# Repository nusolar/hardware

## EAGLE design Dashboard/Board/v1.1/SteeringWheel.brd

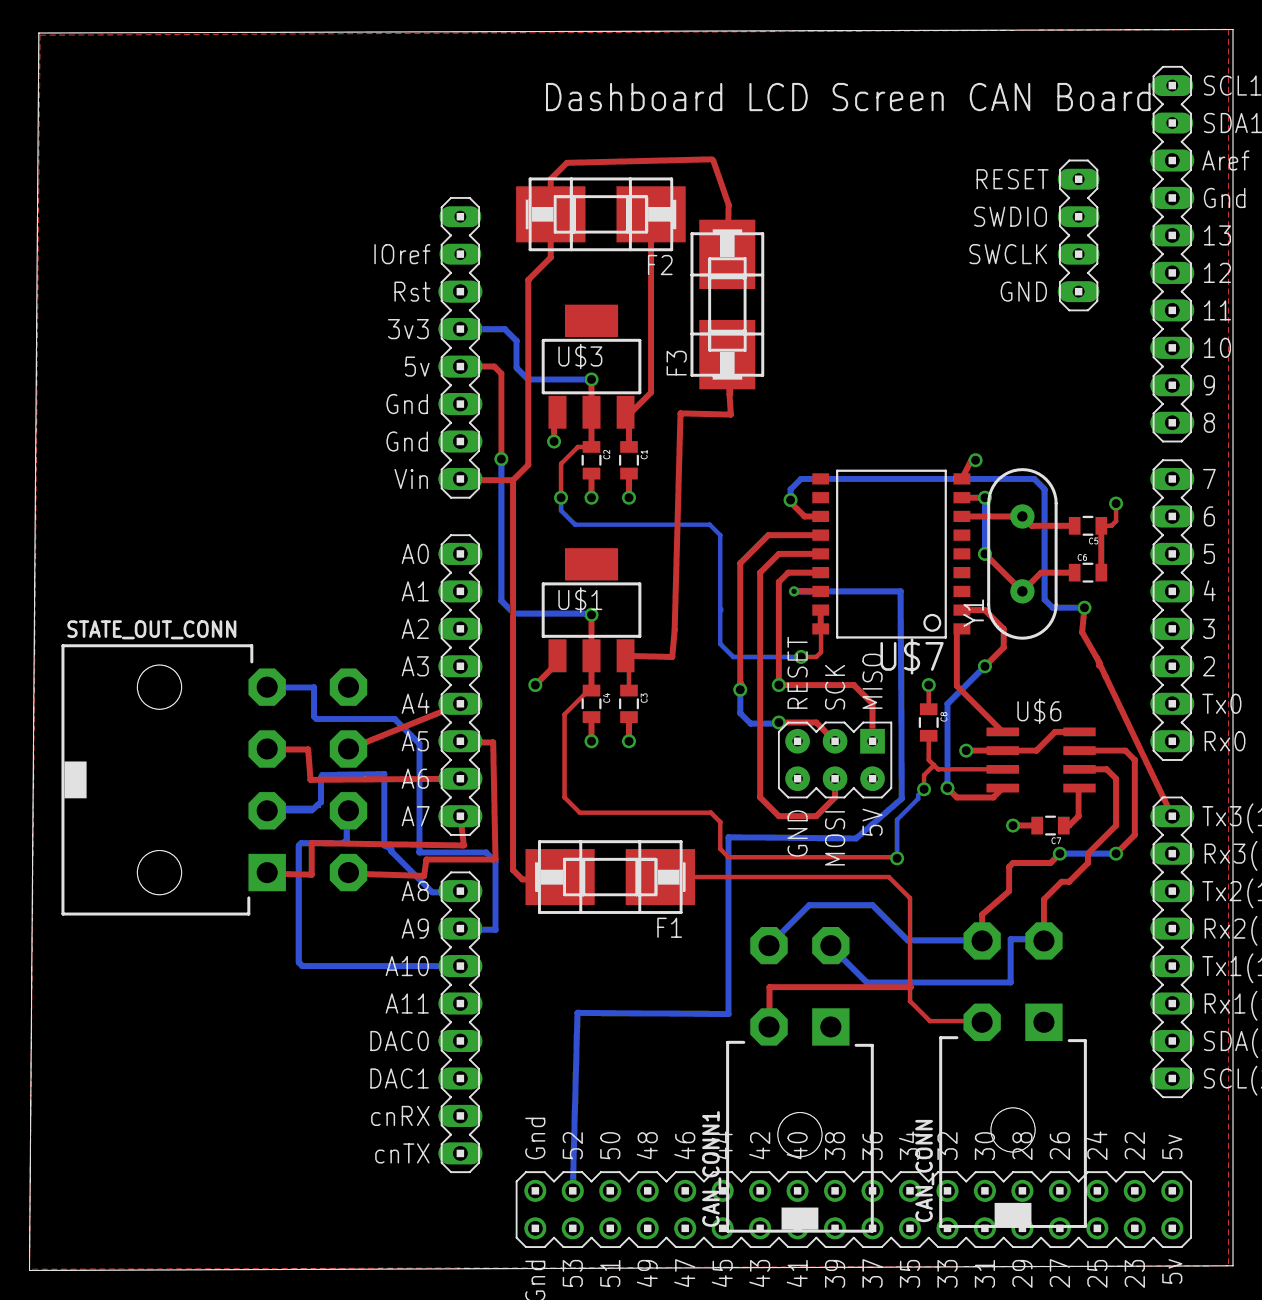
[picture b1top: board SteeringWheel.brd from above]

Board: 2 copper layers, 81.6 x 84.1 mm, 20 parts (0 on the bottom side), 25 nets.

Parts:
C1, C2, C3, C4, C7, C8: .1µF; 0805
C5, C6: 0805
CAN_CONN, CAN_CONN1: 39-30-04?; 39-30-?04?
F1, F2, F3: SMD-MICRO-FUSE-BLOCK; OMNIBLOK
STATE_OUT_CONN: 39-30-08?; 39-30-?08?
U$1: NCP1117ST50T3G; SOT223
U$2: DUE(NORMAL)
U$3: NCP1117ST33T3G; SOT223
U$6: MCP2562; SOIC8
U$7: MCP2515; SO-18W
Y1: HC49US

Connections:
3.3V: C2.1, C7.1, U$2.3V3, U$3.2, U$6.5, U$7.17, U$7.18
5V: C4.1, C8.2, U$1.2, U$2.5V, U$6.3
12V: F1.P$2, F2.P$2, F3.P$2, U$2.VIN
BRK: STATE_OUT_CONN.3, U$2.A6
CAN+: CAN_CONN.2, CAN_CONN1.2, F1.P$1
CAN_CS: U$2.52, U$7.16
CAN_H: CAN_CONN.4, CAN_CONN1.4, U$6.7
CAN_INT: U$2.TX3, U$7.12
CAN_L: CAN_CONN.3, CAN_CONN1.3, U$6.6
CAN_RX: U$6.4, U$7.2
CAN_TX: U$6.1, U$7.1
GND: C1.2, C2.2, C3.2, C4.2, C5.1, C6.2, C7.2, C8.1, CAN_CONN.1, CAN_CONN1.1, U$1.1, U$2.GND_1, U$2.GND_2, U$3.1, U$6.2, U$6.8, U$7.9
HAZ: STATE_OUT_CONN.5, U$2.A5
HD: STATE_OUT_CONN.7, U$2.A4
HRN: STATE_OUT_CONN.2, U$2.A8
LT: STATE_OUT_CONN.4, U$2.A9
MISO: U$2.MISO_ICSP, U$7.15
MOSI: U$2.MOSI_ICSP, U$7.14
unnamed: C3.1, F3.P$1, U$1.3
unnamed: C1.1, F2.P$1, U$3.3
unnamed: C5.2, U$7.7, Y1.2
unnamed: C6.1, U$7.8, Y1.1
RT: STATE_OUT_CONN.6, U$2.A10
SCK: U$2.SCK_ICSP, U$7.13
STRB: STATE_OUT_CONN.1, U$2.A7

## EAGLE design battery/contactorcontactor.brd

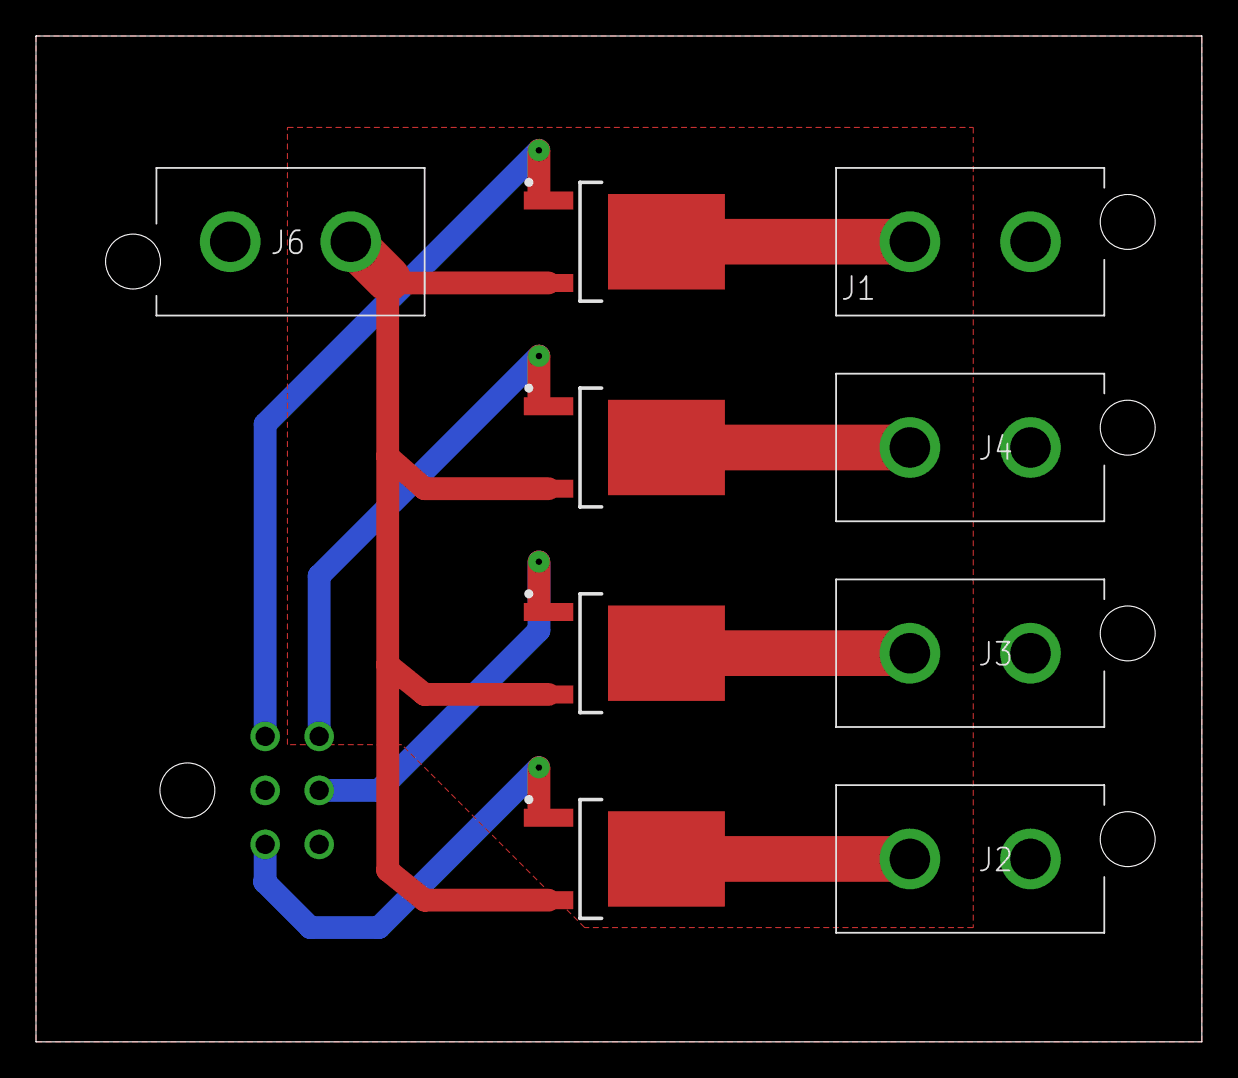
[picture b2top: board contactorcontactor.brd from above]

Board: 2 copper layers, 64.8 x 55.9 mm, 10 parts (1 on the bottom side), 10 nets.

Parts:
J1, J2, J3, J4, J6: 15-31-1026; 15311026
J5: 0430450600; 0430450601
Q1, Q2, Q3, Q4: SPD04P10PL_G; TO229P994X241-3N

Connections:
ASDF: J5.1, Q1.1
GND: J1.2, J2.2, J3.2, J4.2, J5.6, J6.2
unnamed: J2.1, Q2.2
unnamed: J3.1, Q4.2
unnamed: J4.1, Q3.2
unnamed: J1.1, Q1.2
unnamed: J6.1, Q1.3, Q2.3, Q3.3, Q4.3
unnamed: J5.5, Q4.1
unnamed: J5.3, Q2.1
unnamed: J5.4, Q3.1

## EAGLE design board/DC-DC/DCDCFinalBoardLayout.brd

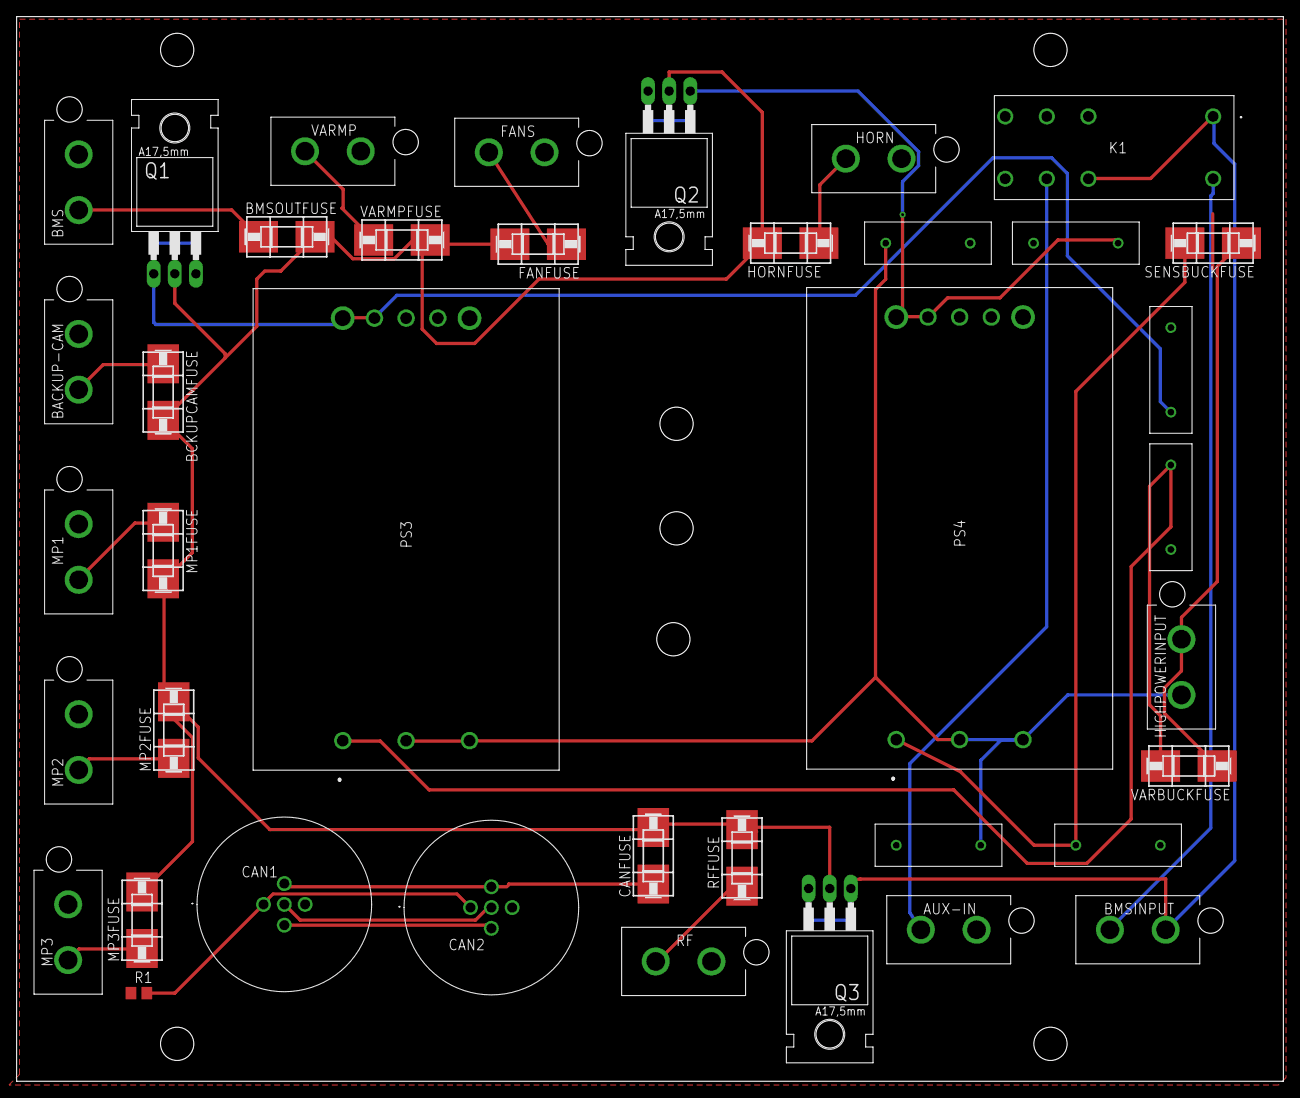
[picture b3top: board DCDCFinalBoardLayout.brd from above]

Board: 2 copper layers, 152.3 x 128.0 mm, 39 parts (0 on the bottom side), 24 nets.

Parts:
AUX-IN: 15-31-1026; 15311026
BACKUP-CAM: 15-31-1026; 15311026
BCKUPCAMFUSE: .25; OMNIBLOK
BMS: 15-31-1026; 15311026
BMSINPUT: 15-31-1026; 15311026
BMSOUTFUSE: 1.2A; OMNIBLOK
CAN1, CAN2: 1200845179
CANFUSE: 1.3 A; OMNIBLOK
FANFUSE: 6 A; OMNIBLOK
FANS: 15-31-1026; 15311026
HIGHPOWERINPUT: 15-31-1026; 15311026
HORN: 15-31-1026; 15311026
HORNFUSE: 1.5 A; OMNIBLOK
K1: ALZ12B12W
MP1, MP2, MP3: 15-31-1026; 15311026
MP1FUSE, MP2FUSE, MP3FUSE: 1A; OMNIBLOK
PS3, PS4: IRQ-12_8.3-T110N-C; IRQ1283T110NC
Q1, Q2, Q3: BUZ10; TO220
R1: 0; R0805
RF: 15-31-1026; 15311026
RFFUSE: 0.4 A; OMNIBLOK
SENSBUCKFUSE: 2A; OMNIBLOK
U$1, U$3, U$4, U$5, U$7, U$8: 4700PF; Y2_CAP
VARBUCKFUSE: 2A; OMNIBLOK
VARMP: 15-31-1026; 15311026
VARMPFUSE: 0.7 A; OMNIBLOK

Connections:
12V: BCKUPCAMFUSE.P$2, BMSOUTFUSE.P$2, CANFUSE.P$2, FANFUSE.P$2, HORNFUSE.P$2, MP1FUSE.P$2, MP2FUSE.P$2, MP3FUSE.P$2, Q1.2, Q2.2, Q3.2, RFFUSE.P$2, VARMPFUSE.P$2
CAN+: BACKUP-CAM.1, BCKUPCAMFUSE.P$1
GND: AUX-IN.2, BACKUP-CAM.2, BMS.2, CAN1.3, CAN2.3, FANS.2, HORN.2, MP1.2, MP2.2, MP3.2, PS3.4, PS3.5, PS4.4, PS4.5, R1.1, RF.2, U$1.P$2, U$3.P$2, U$4.P$1, U$5.P$1, U$7.P$1, U$8.P$1, VARMP.2
IN(-): HIGHPOWERINPUT.1, PS3.2, PS3.3, PS4.2, PS4.3, U$1.P$1, U$3.P$1
IN+: HIGHPOWERINPUT.2, SENSBUCKFUSE.P$1, VARBUCKFUSE.P$1
unnamed: HORN.1, HORNFUSE.P$1
unnamed: AUX-IN.1, K1.6
unnamed: BMSINPUT.1, K1.8
unnamed: BMSINPUT.2, K1.1, K1.7, Q3.1, Q3.3
unnamed: PS3.1, U$7.P$2, VARBUCKFUSE.P$2
unnamed: VARMP.1, VARMPFUSE.P$1
unnamed: RF.1, RFFUSE.P$1
unnamed: FANFUSE.P$1, FANS.1
unnamed: PS4.1, SENSBUCKFUSE.P$2, U$4.P$2
unnamed: BMS.1, BMSOUTFUSE.P$1
unnamed: MP2.1, MP2FUSE.P$1
unnamed: MP3.1, MP3FUSE.P$1
unnamed: PS3.7, PS3.8, Q1.1, Q1.3, U$8.P$2
unnamed: MP1.1, MP1FUSE.P$1
unnamed: PS4.7, PS4.8, Q2.1, Q2.3, U$5.P$2
unnamed: CAN1.1, CAN2.1, R1.2
unnamed: CAN1.4, CAN2.4
unnamed: CAN1.5, CAN2.5
unnamed: CAN1.2, CAN2.2, CANFUSE.P$1

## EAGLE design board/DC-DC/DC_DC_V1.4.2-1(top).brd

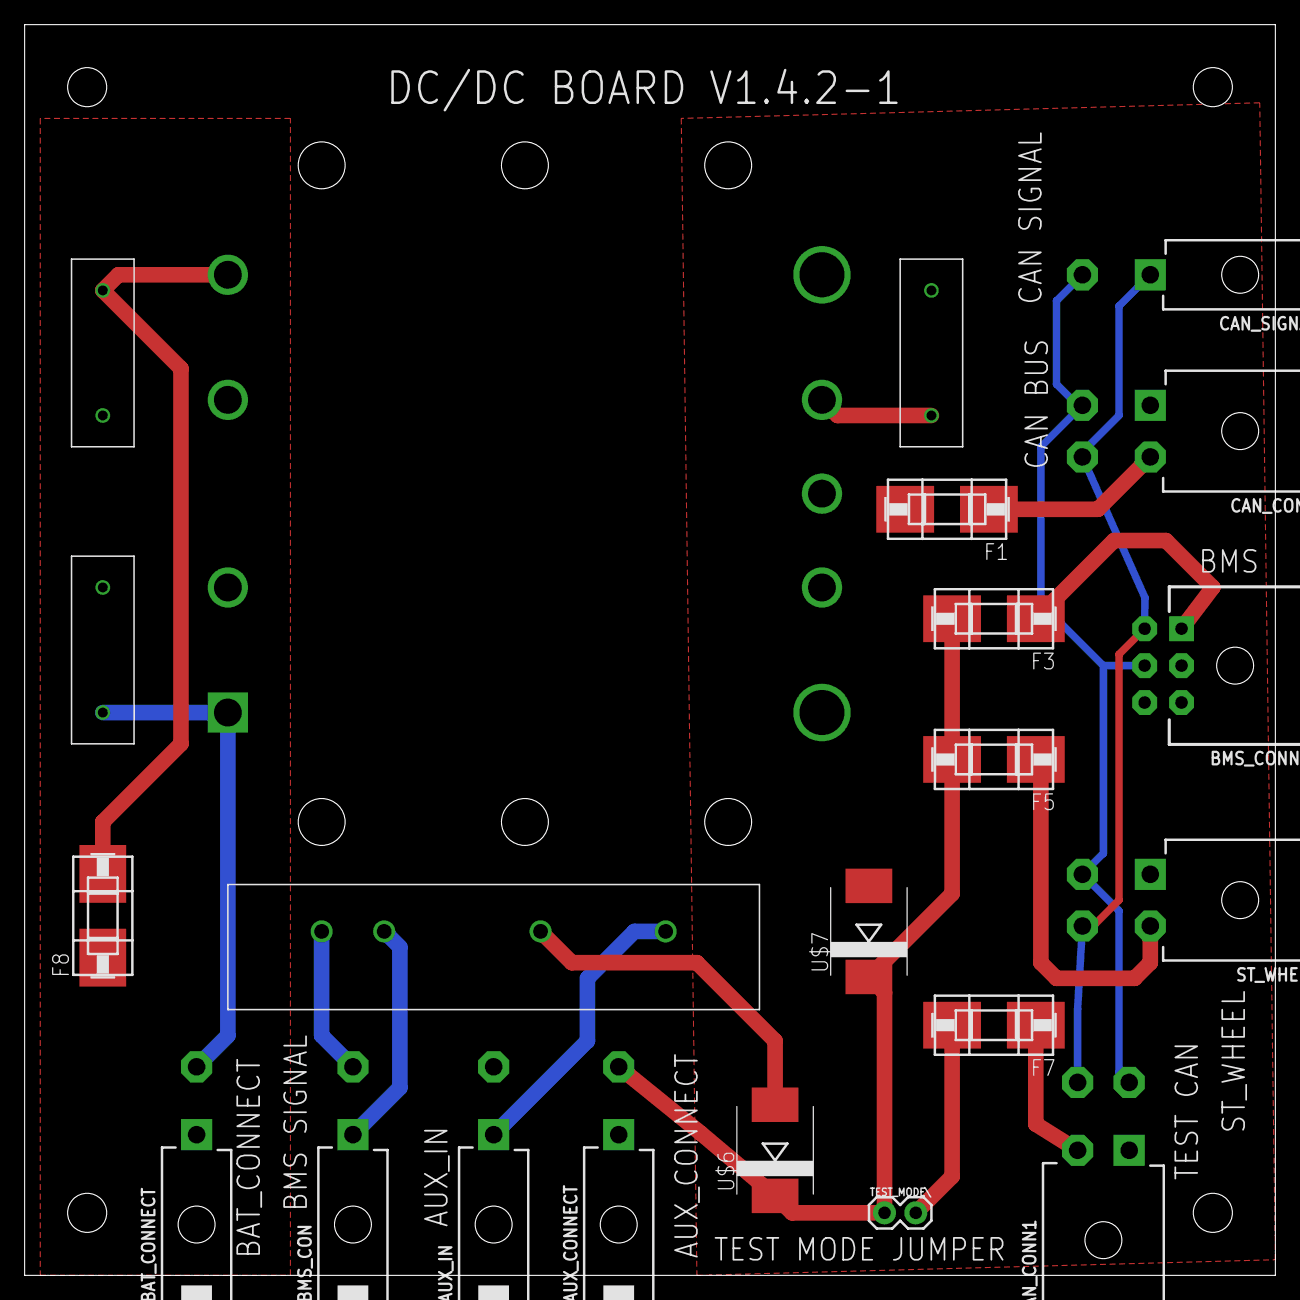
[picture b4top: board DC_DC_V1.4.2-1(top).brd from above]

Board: 2 copper layers, 101.6 x 101.6 mm, 22 parts (0 on the bottom side), 17 nets.

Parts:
AUX_CONNECT: 39-30-02?_S; 39-30-?02?
AUX_IN: 39-30-02?_S; 39-30-?02?
BAT_CONNECT: 39-30-02?_S; 39-30-?02?
BMS_CON: 39-30-02?_S; 39-30-?02?
BMS_CONN: 43045-06
CAN_CONN, CAN_CONN1: 39-30-04?; 39-30-?04?
CAN_SIGNAL: 39-30-02?_S; 39-30-?02?
F1, F7: 4A; OMNIBLOK
F3: 1.5A; OMNIBLOK
F5: 1A; OMNIBLOK
F8: 2A; OMNIBLOK
ST_WHEEL: 39-30-04?; 39-30-?04?
TEST_MODE\: 1X02
U$2: MPDCD3B
U$6, U$7: SL44HE3; SMC
U$8, U$9, U$10: 4700PF; Y2_CAP
U$11: VI-JT1-EW; VI-J00

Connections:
12V: F1.P$2, U$7.A, U$10.P$2, U$11.P$8, U$11.P$9
AUX_12V: AUX_CONNECT.2, F3.P$2, F5.P$2, TEST_MODE\.1, U$6.C, U$7.C
CAN+: CAN_CONN.2, F1.P$1
CAN_H: BMS_CONN.4, CAN_CONN.4, CAN_CONN1.4, CAN_SIGNAL.1, ST_WHEEL.4
CAN_L: BMS_CONN.5, CAN_CONN.3, CAN_CONN1.3, CAN_SIGNAL.2, ST_WHEEL.3
GND: AUX_CONNECT.1, AUX_IN.2, BMS_CONN.2, CAN_CONN.1, CAN_CONN1.1, ST_WHEEL.1, U$8.P$2, U$9.P$1, U$10.P$1, U$11.P$5, U$11.P$6
IN+: BAT_CONNECT.1, F8.P$1
IN-: BAT_CONNECT.2, U$8.P$1, U$11.P$1
unnamed: AUX_IN.1, U$2.P$1
unnamed: BMS_CON.1, U$2.P$3
unnamed: BMS_CON.2, U$2.P$4
unnamed: U$2.P$2, U$6.A
unnamed: BMS_CONN.1, F3.P$1
unnamed: F5.P$1, ST_WHEEL.2
unnamed: CAN_CONN1.2, F7.P$1
unnamed: F8.P$2, U$9.P$2, U$11.P$4
unnamed: F7.P$2, TEST_MODE\.2

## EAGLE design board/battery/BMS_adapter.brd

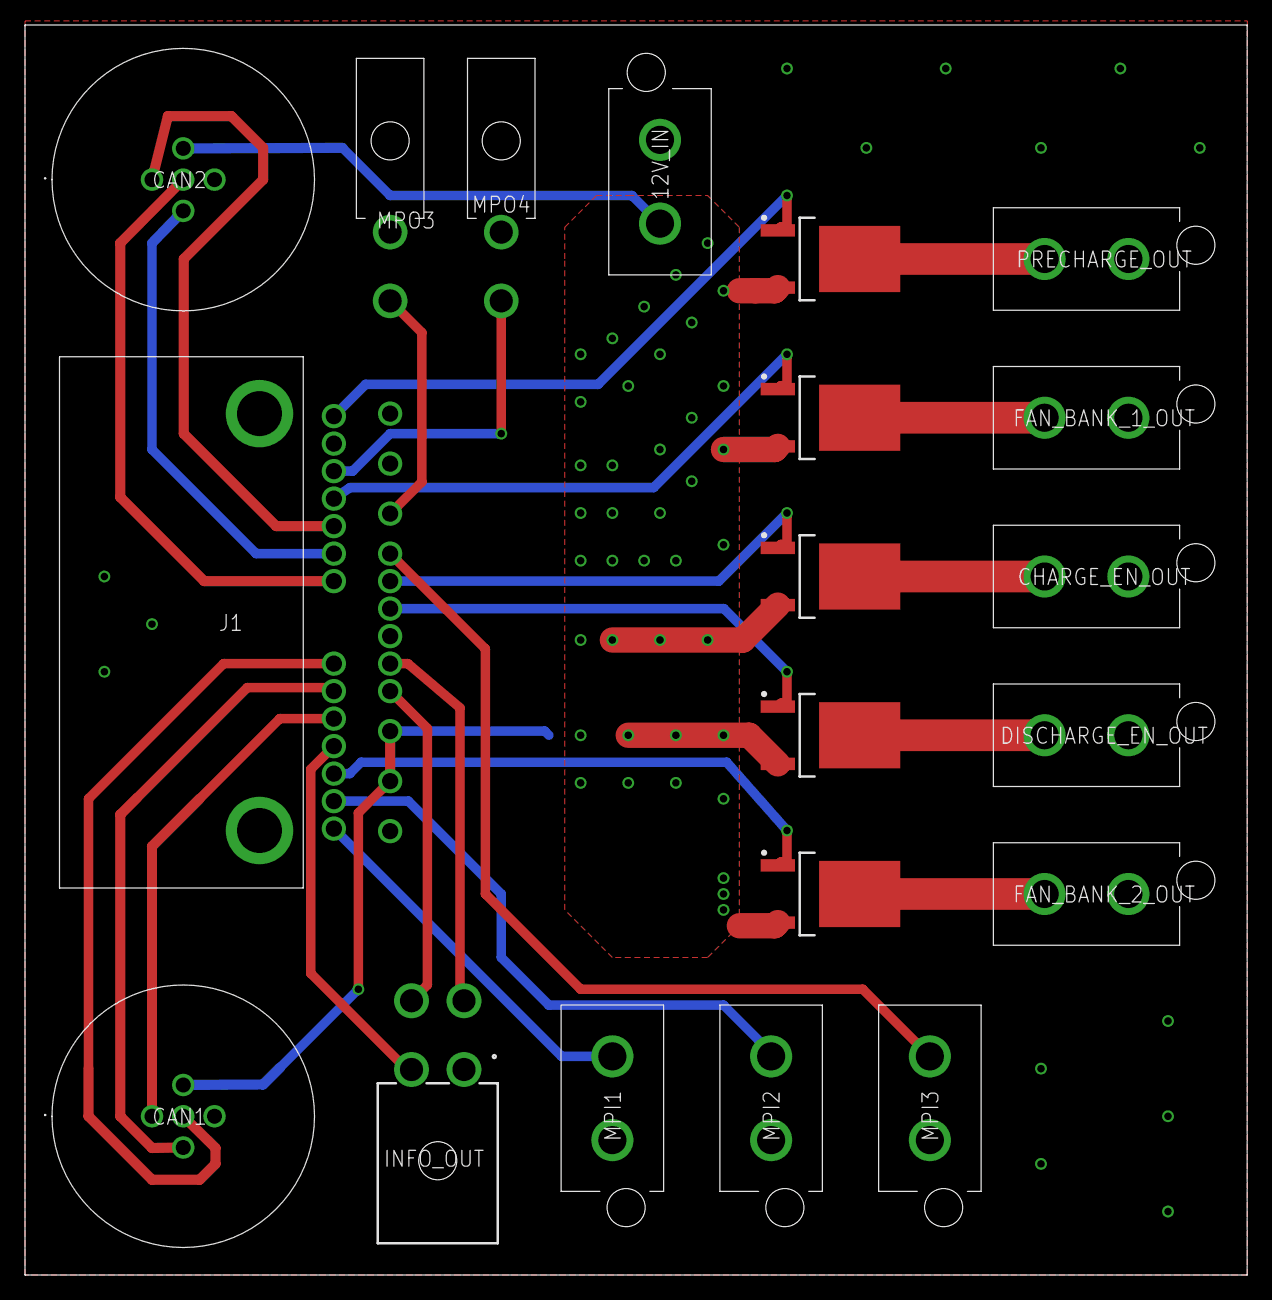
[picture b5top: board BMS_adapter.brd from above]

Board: 2 copper layers, 97.8 x 100.0 mm, 20 parts (0 on the bottom side), 26 nets.

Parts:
12V_IN: 15-31-1026; 15311026
CAN1, CAN2: 1200845179
CHARGE_EN_MOS: SPD04P10PL_G; TO229P994X241-3N
CHARGE_EN_OUT: 15-31-1026; 15311026
DISCHARGE_EN_MOS: SPD04P10PL_G; TO229P994X241-3N
DISCHARGE_EN_OUT: 15-31-1026; 15311026
FAN_BANK_1_MOS, FAN_BANK_2_MOS: SPD04P10PL_G; TO229P994X241-3N
FAN_BANK_1_OUT, FAN_BANK_2_OUT: 15-31-1026; 15311026
INFO_OUT: 26-01-3115; 39-30-1040
J1: 1376357-3; 13763573
MPI1, MPI2, MPI3: 15-31-1026; 15311026
MPO3, MPO4: 26-01-3114; 0026013114
PRECHARGE_MOS: SPD04P10PL_G; TO229P994X241-3N
PRECHARGE_OUT: 15-31-1026; 15311026

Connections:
12V: 12V_IN.1, CAN1.2, CAN2.2, CHARGE_EN_MOS.3, DISCHARGE_EN_MOS.3, FAN_BANK_1_MOS.3, FAN_BANK_2_MOS.3, J1.2, J1.3, PRECHARGE_MOS.3
CAN1_H: CAN1.4, J1.18
CAN1_L: CAN1.5, J1.19
CAN1_SHIELD: CAN1.1, J1.17
CAN2_H: CAN2.4, J1.21
CAN2_L: CAN2.5, J1.20
CAN2_SHIELD: CAN2.1, J1.22
GND: 12V_IN.2, CAN1.3, CAN2.3, CHARGE_EN_OUT.2, DISCHARGE_EN_OUT.2, FAN_BANK_1_OUT.2, FAN_BANK_2_OUT.2, INFO_OUT.1, J1.12, J1.MH1, J1.MH2, MPI1.2, MPI2.2, MPI3.2, MPO3.2, PRECHARGE_OUT.2
unnamed: J1.26, PRECHARGE_MOS.1
unnamed: FAN_BANK_1_MOS.1, J1.23
unnamed: FAN_BANK_2_MOS.1, J1.15
unnamed: DISCHARGE_EN_MOS.1, J1.7
unnamed: J1.10, MPO3.1
unnamed: J1.9, MPI3.1
unnamed: J1.13, MPI1.1
unnamed: J1.14, MPI2.1
unnamed: J1.24, MPO4.1
unnamed: INFO_OUT.3, J1.5
unnamed: INFO_OUT.4, J1.4
unnamed: INFO_OUT.2, J1.16
unnamed: FAN_BANK_1_MOS.2, FAN_BANK_1_OUT.1
unnamed: DISCHARGE_EN_MOS.2, DISCHARGE_EN_OUT.1
unnamed: CHARGE_EN_MOS.1, J1.8
unnamed: FAN_BANK_2_MOS.2, FAN_BANK_2_OUT.1
unnamed: CHARGE_EN_MOS.2, CHARGE_EN_OUT.1
unnamed: PRECHARGE_MOS.2, PRECHARGE_OUT.1

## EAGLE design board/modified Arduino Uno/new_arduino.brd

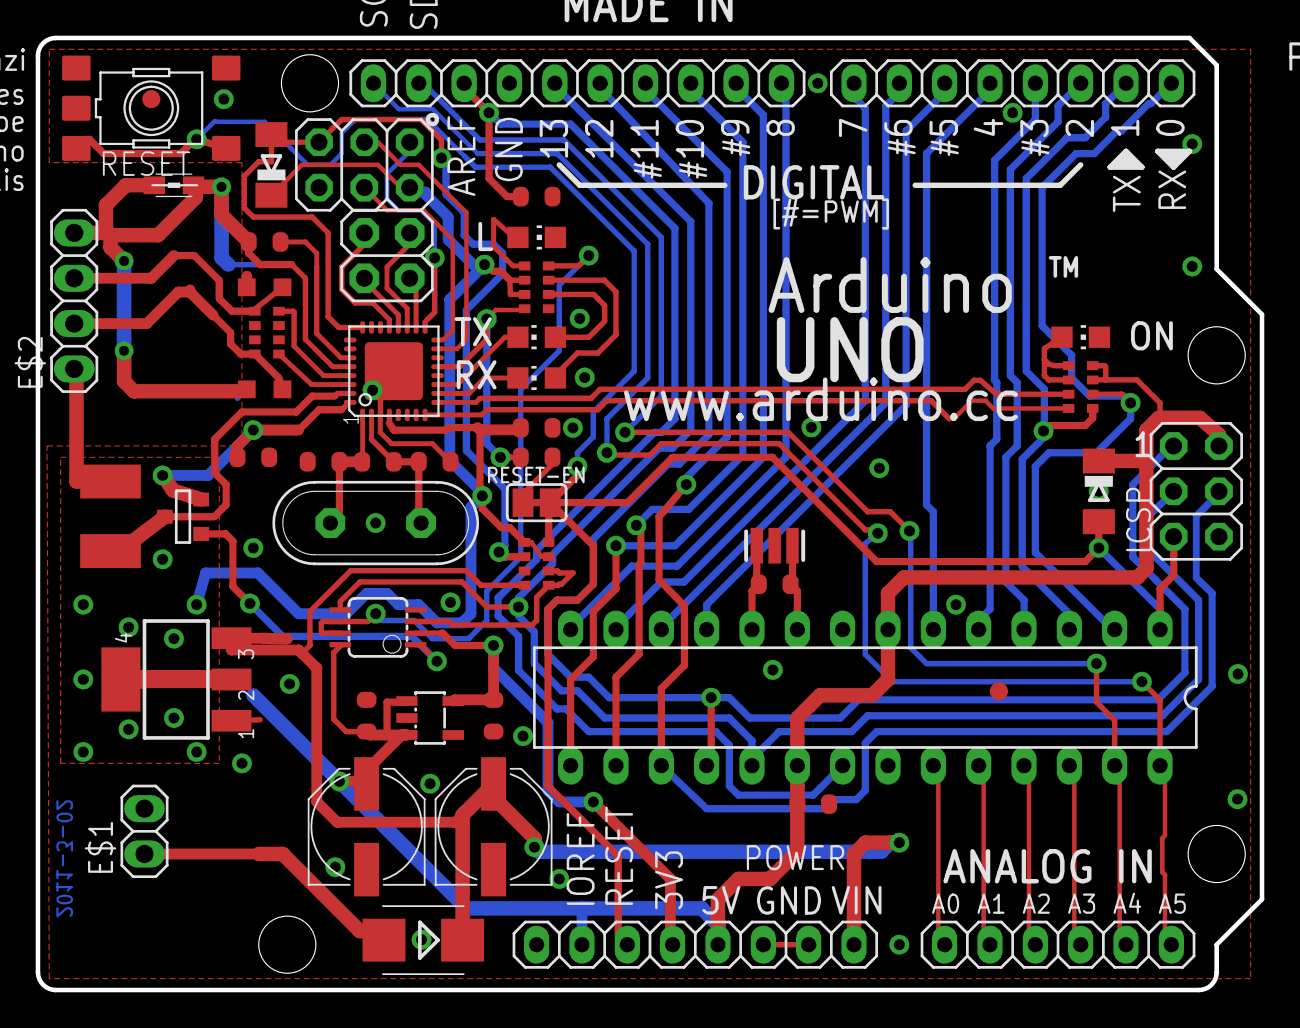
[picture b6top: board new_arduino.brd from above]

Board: 2 copper layers, 68.6 x 53.3 mm, 52 parts (1 on the bottom side), 59 nets.

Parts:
AD: 6x1F-H8.5; 1X06
C1, C2, C4, C5, C6, C7: 100n; C0603-ROUND
C3, C8: 1u; C0603-ROUND
C9, C11: 22p; C0603-ROUND
D1: M7; SMB
D2, D3: CD1206-S01575; MINIMELF
E$1: 1X02
E$2: 1X04
F1: MF-MSMF050-2 500mA; L1812
FD1, FD2: FIDUCIALMOUNT; FIDUCIA-MOUNT
GROUND: SJ
ICSP, ICSP1: 3x2 M; 2X03
IOH: 10x1F-H8.5; 1X10
IOL: 8x1F-H8.5; 1X08
JP2: 2x2 M - NM; 2X02
L: YELLOW; CHIP-LED0805
L1: BLM21; 0805
ON: GREEN; CHIP-LED0805
PC1, PC2: 47u; PANASONIC_D
POWER: 8x1F-H8.5; 1X08
R1, R2: 1M; R0603-ROUND
RESET: TS42031-160R-TR-7260; TS42
RESET-EN: SJ
RN1: 10K; CAY16
RN2, RN4: 1K; CAY16
RN3: 22R; CAY16
RX: YELLOW; CHIP-LED0805
T1: FDN340P; SOT-23
TX: YELLOW; CHIP-LED0805
U1: NCP1117ST50T3G; SOT223
U2: LP2985-33DBVR; SOT23-DBV
U3: ATMEGA16U2-MU(R); MLF32
U5: LMV358IDGKR; MSOP08
U$1: DISCLAIMER
Y1: 16MHz; QS
Y2: CSTCE16M0V53-R0 16MHZ; RESONATOR
Z1, Z2: CG0603MLC-05E; CT/CN0603
ZU4: ATMEGA328P-PU; DIL28-3

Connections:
+3V3: C3.2, POWER.4, U2.5, U5.2
+5V: C1.2, C2.2, C6.2, C7.1, D2.C, D3.C, ICSP.2, ICSP1.2, PC2.+, POWER.2, POWER.5, RN1.3, RN1.5, RN2.2, RN2.3, RN4.3, RN4.4, T1.2, U1.2, U1.4, U2.1, U2.3, U3.4, U3.32, U5.8, ZU4.7, ZU4.20
AD0: AD.1, ZU4.23
AD1: AD.2, ZU4.24
AD2: AD.3, ZU4.25
AD3: AD.4, ZU4.26
AD4/SDA: AD.5, IOH.9, ZU4.27
AD5/SCL: AD.6, IOH.10, ZU4.28
AREF: C4.2, IOH.8, ZU4.21
CMP: RN1.1, RN1.2, U5.3
D+: E$2.3, RN3.5, Z1.1
D-: E$2.2, RN3.8, Z2.1
DTR: C5.1, RN2.4, U3.13
GATE_CMD: T1.3, U5.1
GND: C1.1, C2.1, C3.1, C4.1, C6.1, C7.2, C9.2, C11.2, E$1.2, GROUND.1, ICSP.6, ICSP1.6, IOH.7, L.C, ON.C, PC1.-, PC2.-, POWER.6, POWER.7, RESET.1, RESET.2, RN1.7, RN2.5, U1.1, U2.2, U3.3, U3.33, U5.4, Y2.2, ZU4.8, ZU4.22
IO0: IOL.1, RN4.2, ZU4.2
IO1: IOL.2, RN4.1, ZU4.3
IO2: IOL.3, ZU4.4
IO3: IOL.4, ZU4.5
IO4: IOL.5, ZU4.6
IO5: IOL.6, ZU4.11
IO6: IOL.7, ZU4.12
IO7: IOL.8, ZU4.13
IO8: IOH.1, ZU4.14
IO9: IOH.2, ZU4.15
L13: RN2.8, U5.6, U5.7
M8RXD: RN4.7, U3.9
M8TXD: RN4.8, U3.8
MISO: ICSP.1, IOH.5, ZU4.18
MISO2: ICSP1.1, U3.17
MOSI: ICSP.4, IOH.4, ZU4.17
MOSI2: ICSP1.4, U3.16
unnamed: L.A, RN2.1
unnamed: ON.A, RN4.5, RN4.6
unnamed: RN2.7, RX.A
unnamed: RN2.6, TX.A
PB4: JP2.1, U3.18
PB5: JP2.3, U3.19
PB6: JP2.2, U3.20
PB7: JP2.4, U3.21
PWRIN: D1.A, E$1.1
RD+: RN3.4, U3.29
RD-: RN3.1, U3.30
RESET: C5.2, D2.A, ICSP.5, POWER.3, RESET.3, RESET.4, RESET-EN.1, RESET-EN.2, RN1.4, ZU4.1
RESET2: D3.A, ICSP1.5, RN1.6, U3.24
RXLED: RX.C, U3.10
SCK: ICSP.3, IOH.6, U5.5, ZU4.19
SCK2: ICSP1.3, U3.15
SS: IOH.3, ZU4.16
TP_VUCAP: C8.1, U3.27
TXLED: TX.C, U3.11
UGND: C8.2, E$2.4, GROUND.2, L1.1, L1.2, U3.28, Z1.2, Z2.2
USBVCC: F1.1, T1.1, U3.31
VIN: D1.C, PC1.+, POWER.8, RN1.8, U1.3
XT1: C9.1, R1.1, U3.1, Y1.2
XT2: C11.1, R1.2, U3.2, Y1.1
XTAL1: R2.1, Y2.3, ZU4.9
XTAL2: R2.2, Y2.1, ZU4.10
XUSB: E$2.1, F1.2

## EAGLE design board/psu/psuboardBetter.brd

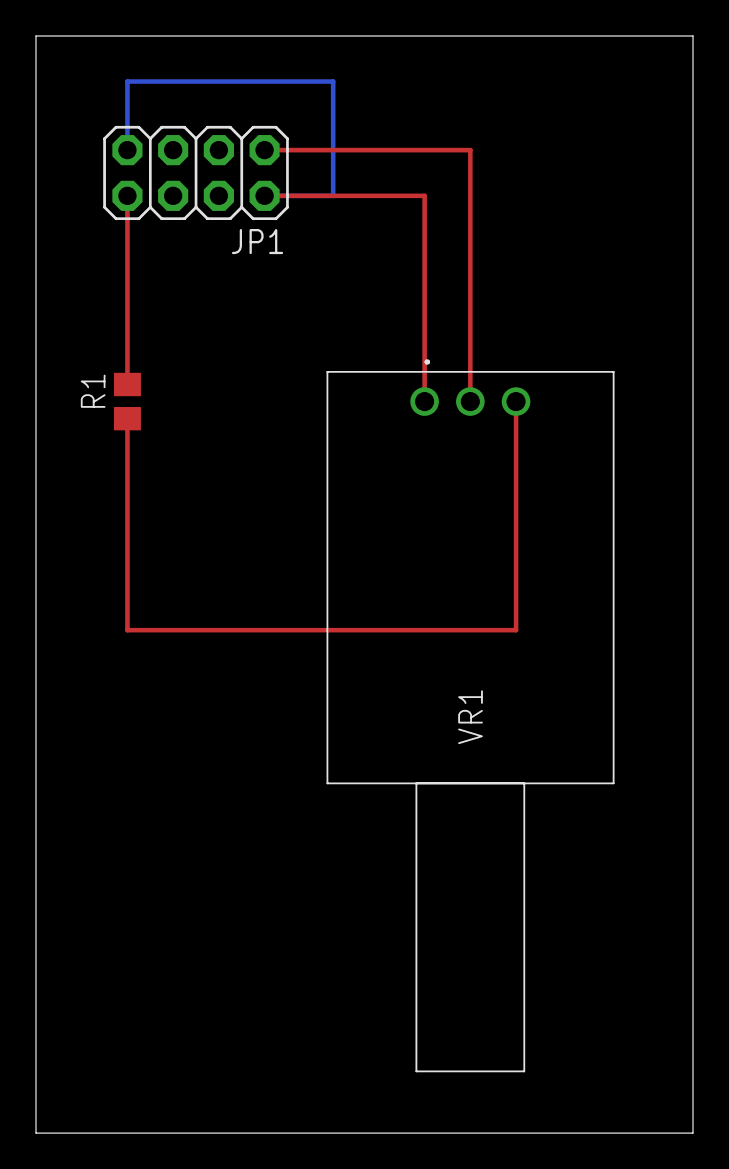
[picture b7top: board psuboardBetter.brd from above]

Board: 2 copper layers, 36.5 x 61.0 mm, 3 parts (0 on the bottom side), 4 nets.

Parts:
JP1: 2X04
R1: 2K; R0805
VR1: 91R1A-R16-A15L; 91R1AR16A15L

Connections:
12V: JP1.8, R1.2
GND: JP1.2, JP1.7, VR1.1
unnamed: R1.1, VR1.3
unnamed: JP1.1, VR1.2

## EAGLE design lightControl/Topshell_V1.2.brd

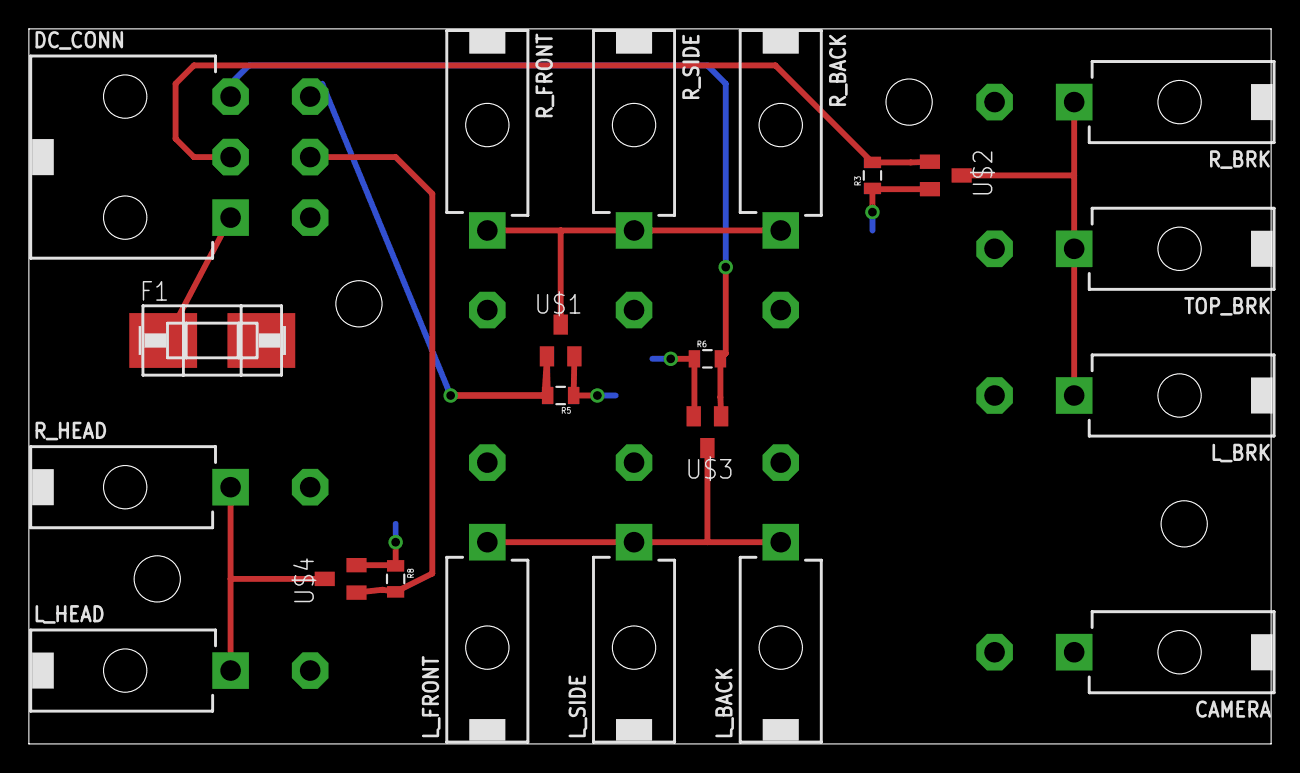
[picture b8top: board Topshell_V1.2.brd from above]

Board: 2 copper layers, 86.0 x 49.5 mm, 22 parts (0 on the bottom side), 11 nets.

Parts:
CAMERA: 39-30-02?; 39-30-?02?
DC_CONN: 39-30-06?; 39-30-?06?
F1: 4A; OMNIBLOK
L_BACK: 39-30-02?; 39-30-?02?
L_BRK: 39-30-02?; 39-30-?02?
L_FRONT: 39-30-02?; 39-30-?02?
L_HEAD: 39-30-02?; 39-30-?02?
L_SIDE: 39-30-02?; 39-30-?02?
R3, R5, R6, R8: 1M; 0805
R_BACK: 39-30-02?; 39-30-?02?
R_BRK: 39-30-02?; 39-30-?02?
R_FRONT: 39-30-02?; 39-30-?02?
R_HEAD: 39-30-02?; 39-30-?02?
R_SIDE: 39-30-02?; 39-30-?02?
TOP_BRK: 39-30-02?; 39-30-?02?
U$1, U$2, U$3, U$4: IRLML6344TRPBF; SOT23

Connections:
12V: CAMERA.2, F1.P$2, L_BACK.2, L_BRK.2, L_FRONT.2, L_HEAD.2, L_SIDE.2, R_BACK.2, R_BRK.2, R_FRONT.2, R_HEAD.2, R_SIDE.2, TOP_BRK.2
GND: CAMERA.1, DC_CONN.4, R3.1, R5.1, R6.1, R8.1, U$1.2, U$2.2, U$3.2, U$4.2
unnamed: DC_CONN.6, R5.2, U$1.1
unnamed: R_BACK.1, R_FRONT.1, R_SIDE.1, U$1.3
unnamed: DC_CONN.2, R3.2, U$2.1
unnamed: L_BRK.1, R_BRK.1, TOP_BRK.1, U$2.3
unnamed: DC_CONN.3, R6.2, U$3.1
unnamed: L_BACK.1, L_FRONT.1, L_SIDE.1, U$3.3
unnamed: DC_CONN.5, R8.2, U$4.1
unnamed: L_HEAD.1, R_HEAD.1, U$4.3
unnamed: DC_CONN.1, F1.P$1

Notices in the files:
parts and their libraries:
SparkFun-Capacitors: Licensing: Creative Commons ShareAlike 4.0 International - https://creativecommons.org/licenses/by-sa/4.0
con-molex-mini-fit: Copyright (C) 2011, Bob Starr
